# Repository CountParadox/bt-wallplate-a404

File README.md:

# Open BT Wallplate (A404)

A Bluetooth-to-network-audio wallplate for a Clipsal C2031VX plate.

- **Audiocom A404** module: Ethernet and network audio (AES67/Dante).
- **ESP32 MiniKit** (ESP-WROOM-32): Bluetooth Classic A2DP sink, sends stereo I²S to the A404.
- **R-Tone RT9400-3.3V**: isolated 3.3 V from 802.3af PoE.

**Status: rev 0.13, prototype draft.** Not yet built or tested. Read [release/r0.13/README.md](release/r0.13/README.md) for the check results and the open items before ordering boards.

## Layout

| Folder | Contents |
|---|---|
| `hardware/` | KiCad 10 project `dt-wp` (schematic, 4-layer PCB, custom DRC rules) and the `A404_Carrier` symbol and footprint libraries |
| `hardware/archive/` | Earlier 2-layer trial boards, kept for reference only |
| `release/r0.13/` | Gerbers, JLCPCB BOM and placement files, full BOM, ERC/DRC reports, render |
| `mechanical/fit-check/` | 1:1 printable dummy board (STL/3MF) for checking module footprints and wall fit |
| `firmware/` | ESP-IDF firmware for the ESP32 (to be added) |
| `docs/` | Design review log |

## Opening the project

Open `hardware/dt-wp.kicad_pro` in KiCad 10. The project-local library tables point at `A404_Carrier.kicad_sym` and `A404_Carrier.pretty` next to it.

## I²S wiring

| Signal | ESP32 | A404 |
|---|---|---|
| Bit clock | GPIO18 | J5.9 SCLK (A404 drives) |
| L/R clock | GPIO19 | J5.10 LRCLK (A404 drives) |
| Data | GPIO23 | J5.5 SDIN0 |

## Releases

Each hardware revision gets a folder under `release/` and a git tag (`hw-r0.13`). Change the KiCad files first, re-run ERC/DRC, then export a new release folder.

## Licence

No licence has been chosen yet.

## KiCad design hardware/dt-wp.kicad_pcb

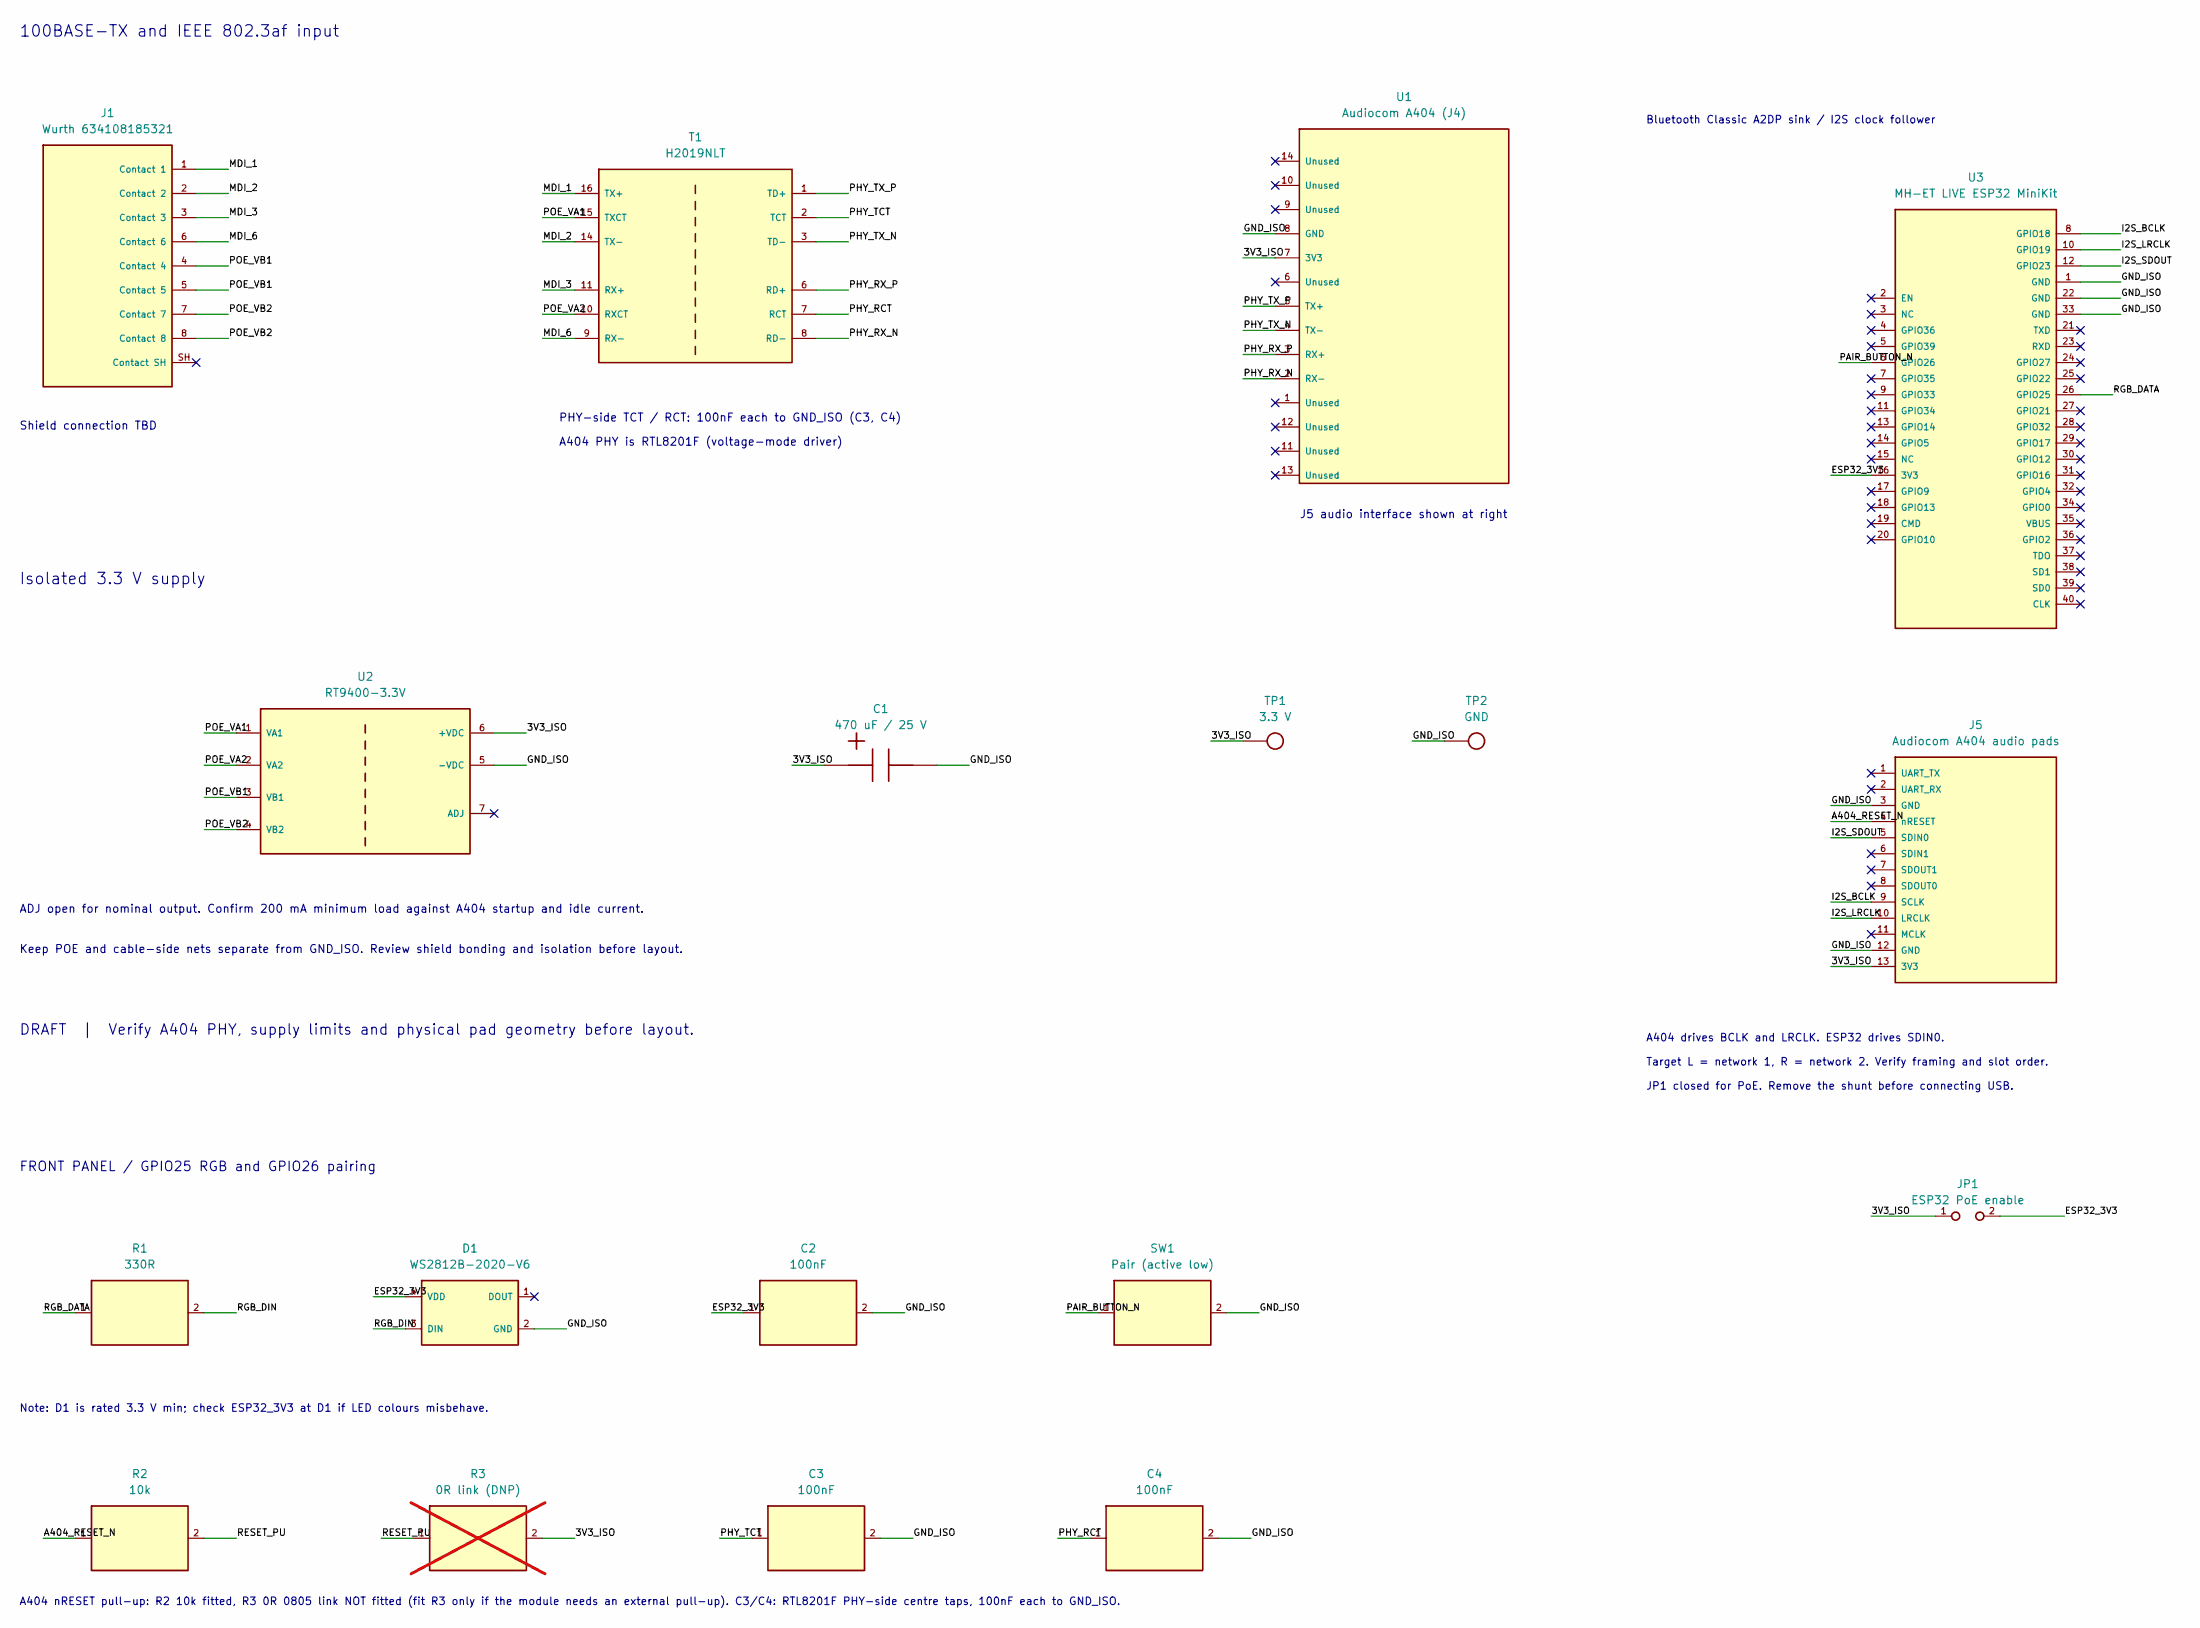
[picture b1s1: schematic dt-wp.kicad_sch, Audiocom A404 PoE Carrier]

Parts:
C1: 470 uF / 25 V; CP_Radial_D8.0mm_P3.50mm
C2, C3, C4: 100nF; C_0603_1608Metric
D1: WS2812B-2020-V6; LED_WS2812B-2020_PLCC4_2.0x2.0mm
J1: Wurth 634108185321; Wurth_634108185321
J5: Audiocom A404 audio pads; A404_J5
JP1: ESP32 PoE enable; PinHeader_1x02_P2.54mm_Vertical
R1: 330R; R_0603_1608Metric
R2: 10k; R_0603_1608Metric
R3: 0R link (DNP); R_0805_2012Metric; not fitted
SW1: Pair (active low); SW_Push_1P1T_NO_CK_PTS125Sx85SMTR
T1: H2019NLT; Pulse_H2019NL
TP1: 3.3 V; TestPoint_Pad_D1.5mm
TP2: GND; TestPoint_Pad_D1.5mm
U1: Audiocom A404 (J4); A404_J4
U2: RT9400-3.3V; RT9400_Decal_51.1mm
U3: MH-ET LIVE ESP32 MiniKit; ESP32_mini

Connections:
/3V3_ISO: C1.1 (+), J5.13 (3V3), JP1.1, R3.2, TP1.1, U1.7 (3V3), U2.6 (+VDC)
/A404_RESET_N: J5.4 (nRESET), R2.1
/ESP32_3V3: C2.1, D1.4 (VDD), JP1.2, U3.16 (3V3)
/GND_ISO: C1.2 (-), C2.2, C3.2, C4.2, D1.2 (GND), J5.3 (GND), J5.12 (GND), SW1.2, TP2.1, U1.8 (GND), U2.5 (-VDC), U3.1 (GND), U3.22 (GND), U3.33 (GND)
/I2S_BCLK: J5.9 (SCLK), U3.8 (GPIO18)
/I2S_LRCLK: J5.10 (LRCLK), U3.10 (GPIO19)
/I2S_SDOUT: J5.5 (SDIN0), U3.12 (GPIO23)
/MDI_1: J1.1 (Contact 1), T1.16 (TX+)
/MDI_2: J1.2 (Contact 2), T1.14 (TX-)
/MDI_3: J1.3 (Contact 3), T1.11 (RX+)
/MDI_6: J1.6 (Contact 6), T1.9 (RX-)
/PAIR_BUTTON_N: SW1.1, U3.6 (GPIO26)
/PHY_RCT: C4.1, T1.7 (RCT)
/PHY_RX_N: T1.8 (RD-), U1.2 (RX-)
/PHY_RX_P: T1.6 (RD+), U1.3 (RX+)
/PHY_TCT: C3.1, T1.2 (TCT)
/PHY_TX_N: T1.3 (TD-), U1.4 (TX-)
/PHY_TX_P: T1.1 (TD+), U1.5 (TX+)
/POE_VA1: T1.15 (TXCT), U2.1 (VA1)
/POE_VA2: T1.10 (RXCT), U2.2 (VA2)
/POE_VB1: J1.4 (Contact 4), J1.5 (Contact 5), U2.3 (VB1)
/POE_VB2: J1.7 (Contact 7), J1.8 (Contact 8), U2.4 (VB2)
/RESET_PU: R2.2, R3.1
/RGB_DATA: R1.1, U3.26 (GPIO25)
/RGB_DIN: D1.3 (DIN), R1.2

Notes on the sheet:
100BASE-TX and IEEE 802.3af input
PHY-side TCT / RCT: 100nF each to GND_ISO (C3, C4)
A404 PHY is RTL8201F (voltage-mode driver)
J5 audio interface shown at right
Shield connection TBD
Isolated 3.3 V supply
ADJ open for nominal output. Confirm 200 mA minimum load against A404 startup and idle current.
Keep POE and cable-side nets separate from GND_ISO. Review shield bonding and isolation before layout.
DRAFT | Verify A404 PHY, supply limits and physical pad geometry before layout.
Bluetooth Classic A2DP sink / I2S clock follower
A404 drives BCLK and LRCLK. ESP32 drives SDIN0.
Target L = network 1, R = network 2. Verify framing and slot order.
JP1 closed for PoE. Remove the shunt before connecting USB.
FRONT PANEL / GPIO25 RGB and GPIO26 pairing
Note: D1 is rated 3.3 V min; check ESP32_3V3 at D1 if LED colours misbehave.
A404 nRESET pull-up: R2 10k fitted, R3 0R 0805 link NOT fitted (fit R3 only if the module needs an external pull-up). C3/C4: RTL8201F PHY-side centre taps, 100nF each to GND_ISO.

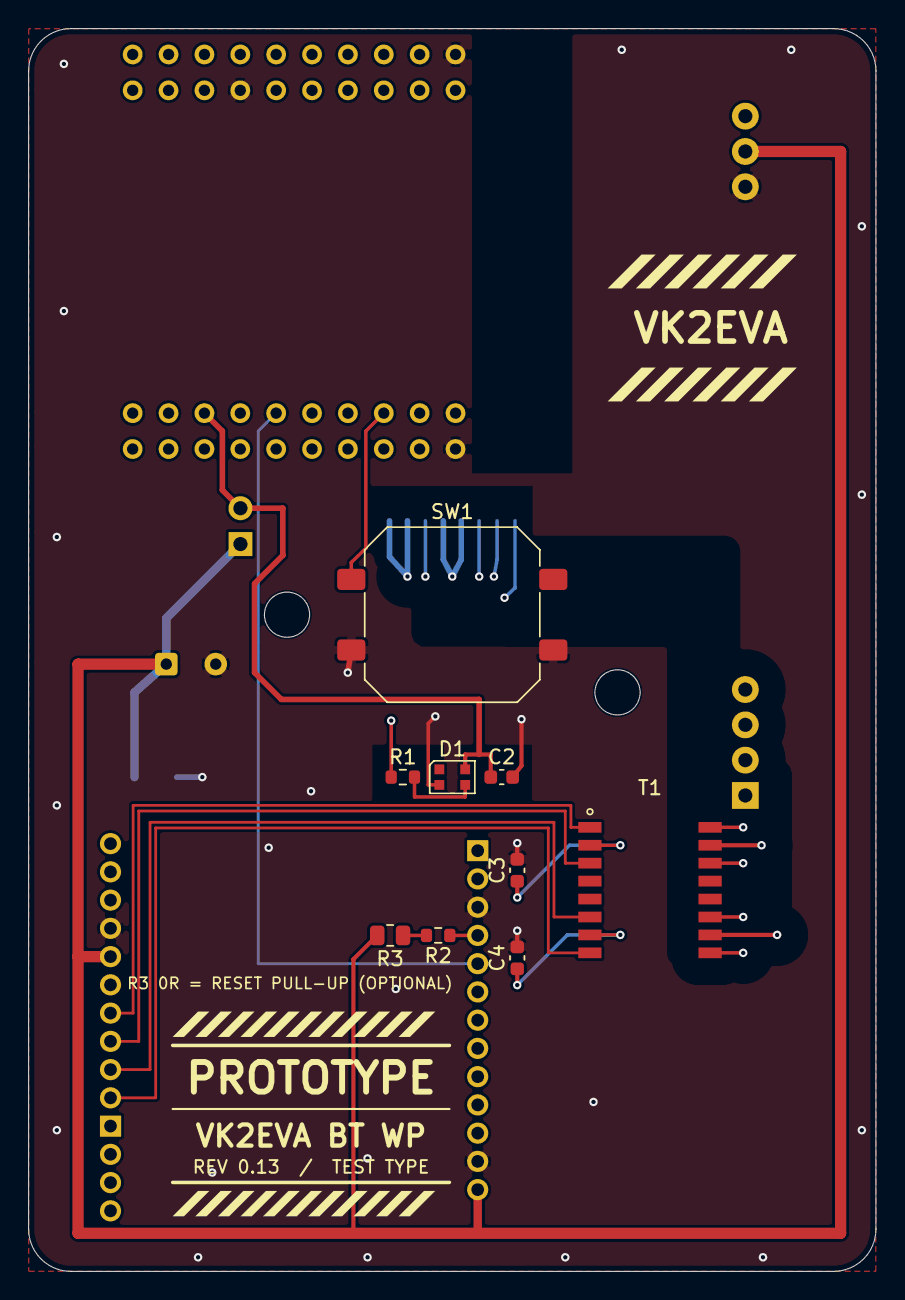
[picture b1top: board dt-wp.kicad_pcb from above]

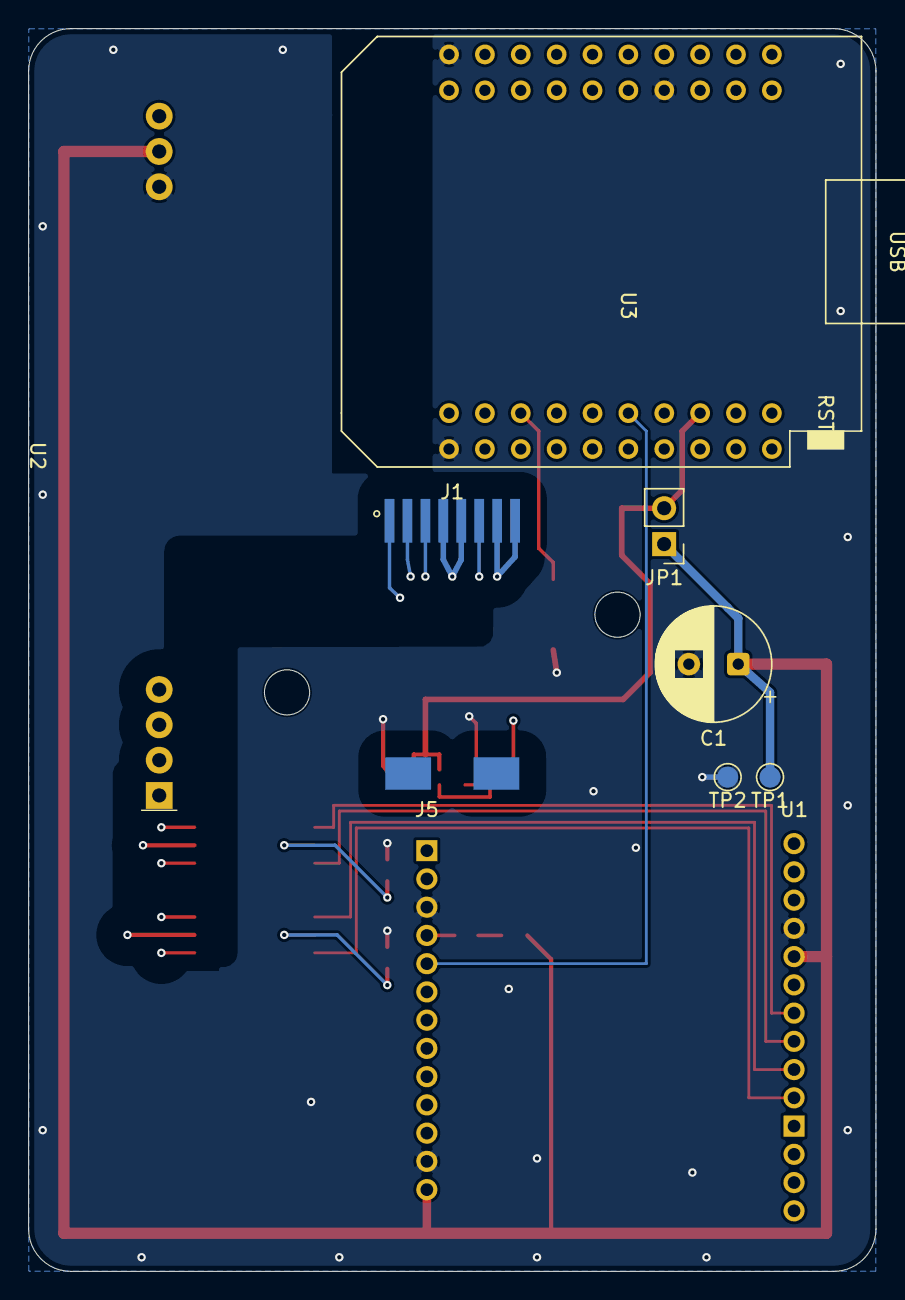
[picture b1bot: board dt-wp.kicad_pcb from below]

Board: 4 copper layers, 60.0 x 88.0 mm, 20 parts (9 on the bottom side), 25 nets.

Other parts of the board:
H1, H2: M3 hole; MountingHole_3.2mm_M3_NoCourtyard
